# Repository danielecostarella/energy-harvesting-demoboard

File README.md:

WSN Demoboard for Energy Harvesting
===================================

This project aims to develop a demonstration board for integration into a Wireless Sensor Network (WSN) using energy harvesting. The board is optimized in terms of hardware and software to ensure low power consumption, enabling it to be powered through Energy Harvesting. The project is focused on exploring the potential of piezoelectric, solar, and thermoelectric sources for energy harvesting.

less Copy code

Getting Started
---------------

To get started with this project, you will need to have the following hardware and software:

### Hardware

* The demoboard itself
* Piezoelectric, solar, and/or thermoelectric sources (depending on your application)

### Software

* Arduino IDE
* Libraries for the specific sensors used in your project

Installation
------------

1.  Clone this repository to your local machine.
2.  Open the project in Arduino IDE.
3.  Install the required libraries.
4.  Compile and upload the sketch to the demoboard.

Usage
-----

Connect the energy harvesting sources to the demoboard and power it up. The board will automatically begin to harvest energy and power the sensors. Use the specific libraries for your sensors to collect data and transmit it to the WSN.

Contributing
------------

Contributions to this project are welcome! If you find any issues or have suggestions for improvement, please submit a pull request or open an issue.

License
-------

This project is licensed under the [MIT License](https://opensource.org/licenses/MIT). See the `LICENSE` file for details.

Acknowledgments
---------------

* This project was developed as part of a thesis by \[Daniele Costarella\].

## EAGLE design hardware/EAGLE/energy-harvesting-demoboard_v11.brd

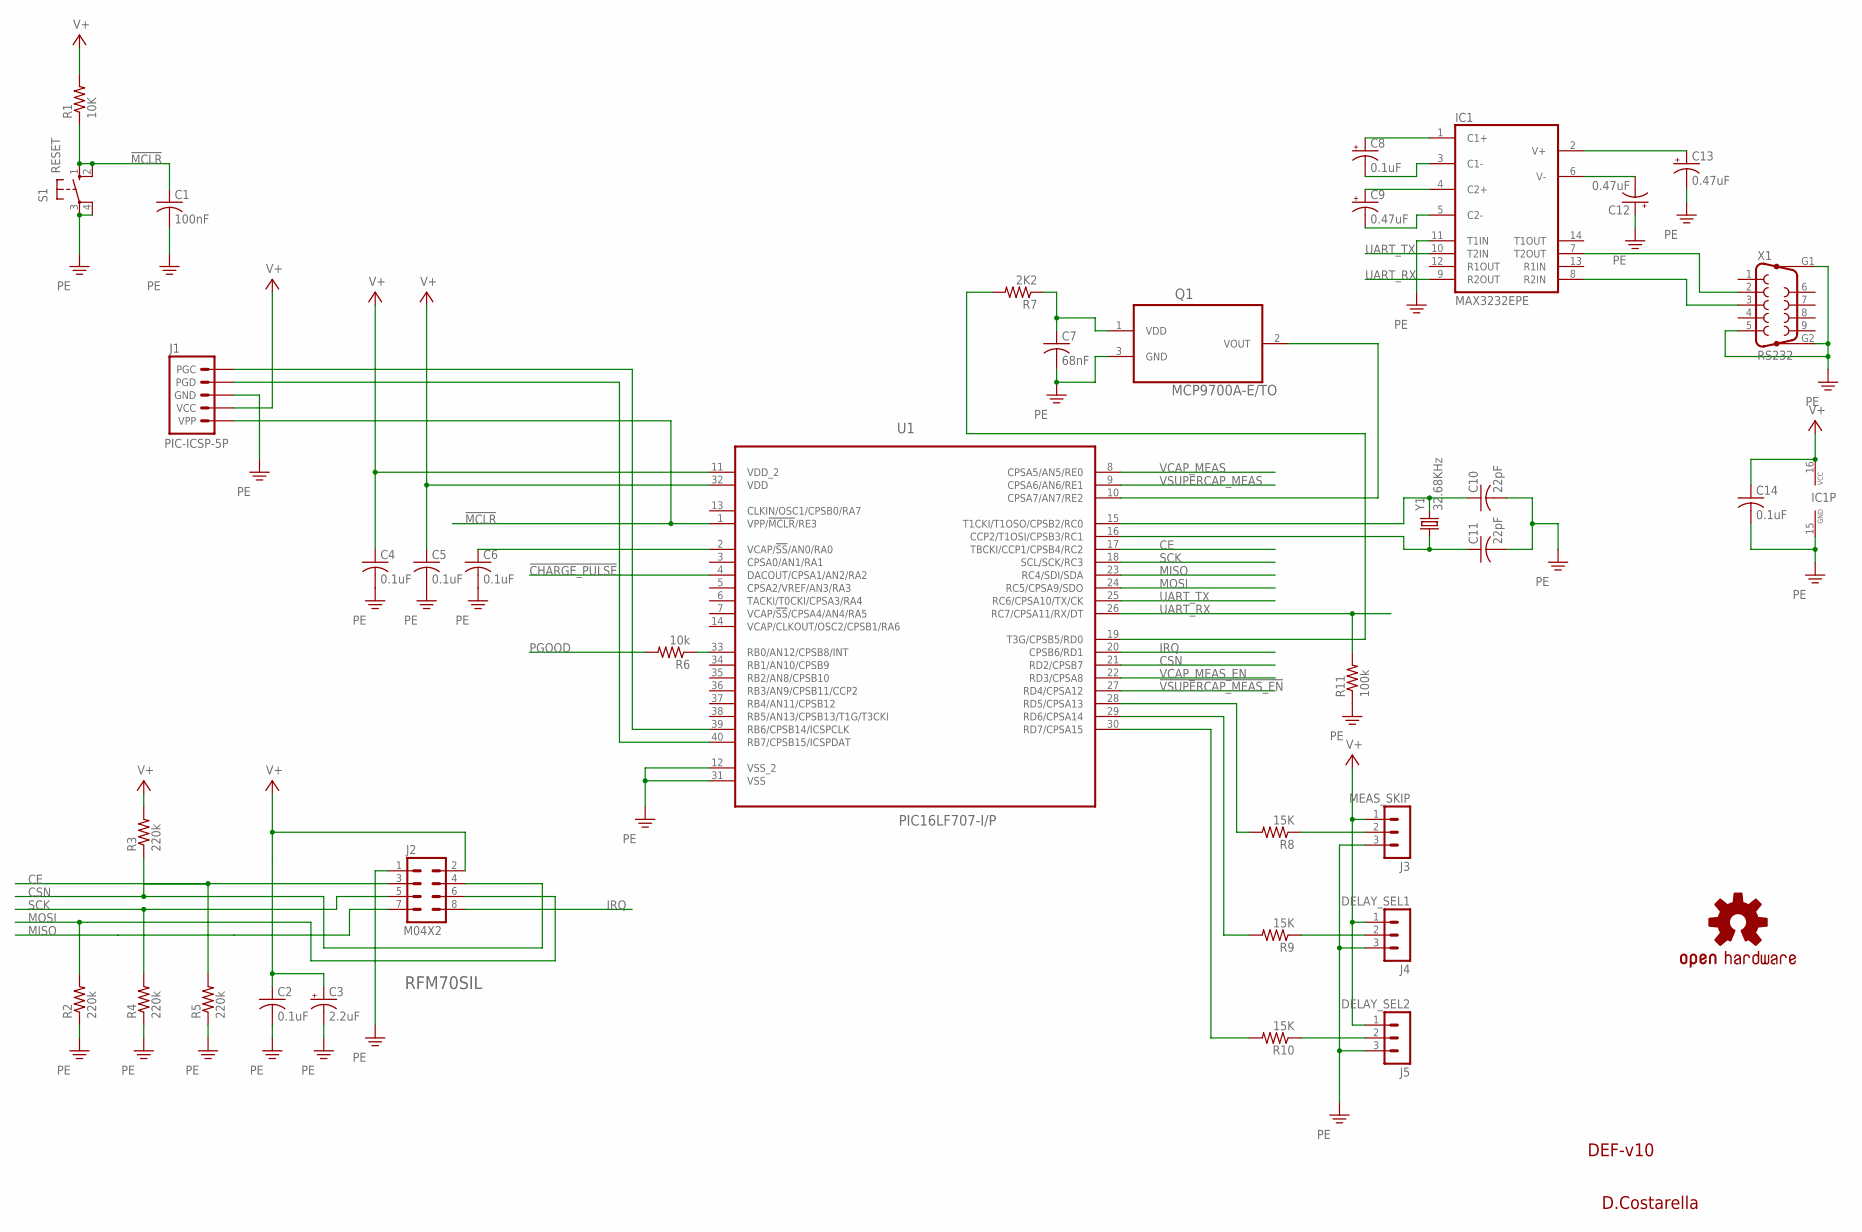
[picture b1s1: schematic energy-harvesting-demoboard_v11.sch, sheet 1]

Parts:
C1: 100nF; C025-025X050
C2, C4, C5, C6: 0.1uF; C050-025X075
C3: 2.2uF; E2,5-5
C7: 68nF; C050-035X075
C8: 0.1uF; E2,5-5
C9, C12, C13: 0.47uF; E2,5-5
C10, C11: 22pF; C025-025X050
C14: 0.1uF; C050-030X075
IC1: MAX3232EPE; DIL16
J1: PIC-ICSP-5P; 1X05
J2: M04X2; 2X4
J3: MEAS_SKIP; MA03-1
J4: DELAY_SEL1; MA03-1
J5: DELAY_SEL2; MA03-1
LOGO1: OSHW-LOGOL; OSHW-LOGO-L
Q1: MCP9700A-E/TO; TO127P254X533-3
R1: 10K; AXIAL-0.4
R2, R3, R4, R5: 220k; AXIAL-0.4
R6: 10k; AXIAL-0.4
R7: 2K2; AXIAL-0.4
R8, R9, R10: 15K; AXIAL-0.4
R11: 100k; AXIAL-0.4
S1: RESET; B3F-10XX
U1: PIC16LF707-I/P; DIP254P1524X635-40
X1: RS232; F09HP
Y1: 32.68KHz; TC26HEZ

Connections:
!CHARGE_PULSE: U1.4 (DACOUT/CPSA1/AN2/RA2); also elsewhere on the board
!MCLR: C1.1, J1.1 (VPP), R1.P$1 (1), S1.1 (S), S1.2 (S1), U1.1 (VPP/!MCLR!/RE3)
!VSUPERCAP_MEAS_EN: U1.27 (RD4/CPSA12); also elsewhere on the board
CE: J2.3, R5.P$2 (2), U1.17 (TBCKI/CCP1/CPSB4/RC2)
CSN: J2.4, R3.P$1 (1), U1.21 (RD2/CPSB7)
IRQ: J2.8, U1.20 (CPSB6/RD1)
MISO: J2.7, U1.23 (RC4/SDI/SDA)
MOSI: J2.6, R2.P$2 (2), U1.24 (RC5/CPSA9/SDO)
unnamed: J1.5 (PGC), U1.39 (RB6/CPSB14/ICSPCLK)
unnamed: J1.4 (PGD), U1.40 (RB7/CPSB15/ICSPDAT)
unnamed: C6.1, U1.2 (VCAP/!SS!/AN0/RA0)
unnamed: C10.1, U1.15 (T1CKI/T1OSO/CPSB2/RC0), Y1.2
unnamed: C11.1, U1.16 (CCP2/T1OSI/CPSB3/RC1), Y1.1
unnamed: Q1.2 (VOUT), U1.10 (CPSA7/AN7/RE2)
unnamed: J3.2, R8.P$1 (1)
unnamed: R8.P$2 (2), U1.28 (RD5/CPSA13)
unnamed: J4.2, R9.P$1 (1)
unnamed: J5.2, R10.P$1 (1)
unnamed: R9.P$2 (2), U1.29 (RD6/CPSA14)
unnamed: R10.P$2 (2), U1.30 (RD7/CPSA15)
unnamed: C7.1, Q1.1 (VDD), R7.P$1 (1)
unnamed: C8.+, IC1.1 (C1+)
unnamed: C8.-, IC1.3 (C1-)
unnamed: C9.+, IC1.4 (C2+)
unnamed: C9.-, IC1.5 (C2-)
unnamed: C12.-, IC1.6 (V-)
unnamed: C13.+, IC1.2 (V+)
unnamed: IC1.8 (R2IN), X1.3
unnamed: IC1.7 (T2OUT), X1.2
unnamed: R6.P$1 (1), U1.33 (RB0/AN12/CPSB8/INT)
PE: C1.2, C2.2, C3.-, C4.2, C5.2, C6.2, C7.2, C10.2, C11.2, C12.+, C13.-, C14.2, IC1.11 (T1IN), IC1.15 (GND), J1.3 (GND), J2.1, J3.3, J4.3, J5.3, Q1.3 (GND), R2.P$1 (1), R4.P$1 (1), R5.P$1 (1), R11.P$1 (1), S1.3, S1.4 (P1), U1.12 (VSS_2), U1.31 (VSS), X1.5, X1.G1, X1.G2; also elsewhere on the board
PGOOD: R6.P$2 (2); also elsewhere on the board
SCK: J2.5, R4.P$2 (2), U1.18 (SCL/SCK/RC3)
SENS_EN: R7.P$2 (2), U1.19 (T3G/CPSB5/RD0)
UART_RX: IC1.9 (R2OUT), R11.P$2 (2), U1.26 (RC7/CPSA11/RX/DT)
UART_TX: IC1.10 (T2IN), U1.25 (RC6/CPSA10/TX/CK)
V+: C2.1, C3.+, C4.1, C5.1, C14.1, IC1.16 (VCC), J1.2 (VCC), J2.2, J3.1, J4.1, J5.1, R1.P$2 (2), R3.P$2 (2), U1.11 (VDD_2), U1.32 (VDD); also elsewhere on the board
VCAP_MEAS: U1.8 (CPSA5/AN5/RE0); also elsewhere on the board
VCAP_MEAS_EN: U1.22 (RD3/CPSA8); also elsewhere on the board
VSUPERCAP_MEAS: U1.9 (CPSA6/AN6/RE1); also elsewhere on the board

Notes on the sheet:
DEF-v10
D.Costarella
RFM70SIL

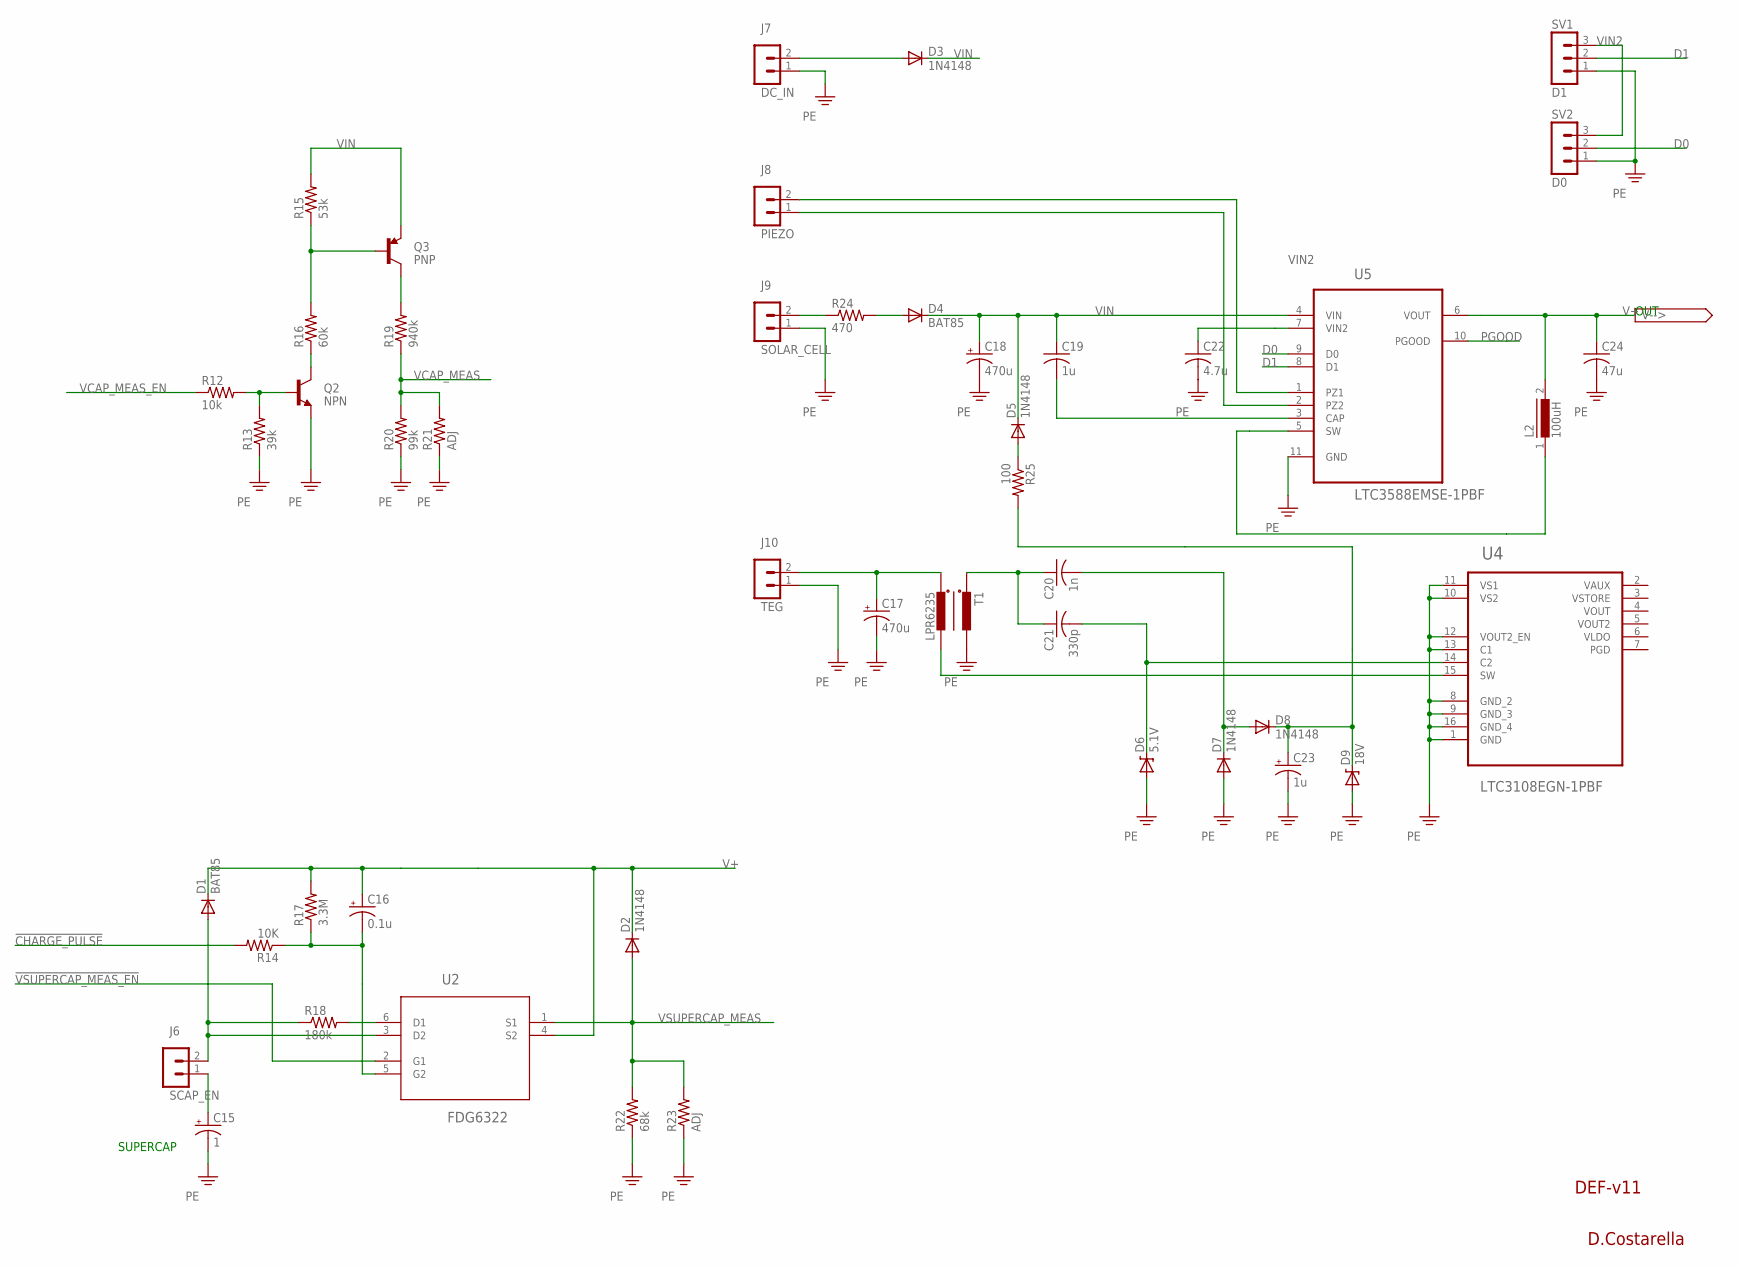
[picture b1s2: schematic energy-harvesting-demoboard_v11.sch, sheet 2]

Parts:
C15: 1; E5-8,5
C16: 0.1u; E2,5-5
C17, C18: 470u; E5-10,5
C19: 1u; C050-035X075
C20: 1n; C050-030X075
C21: 330p; C050-030X075
C22: 4.7u; C025-024X044
C23: 1u; E2,5-6E
C24: 47u; C050-025X075
D1, D4: BAT85; DIODE-1N4148
D2, D7, D8: 1N4148; DIODE-1N4148
D3, D5: 1N4148; SMA-DIODE
D6: 5.1V; DIODE-ZENER
D9: 18V; DIODE-ZENER
J6: SCAP_EN; MA02-1
J7: DC_IN; MA02-1
J8: PIEZO; MA02-1
J9: SOLAR_CELL; MA02-1
J10: TEG; MA02-1
L2: 100uH; DR125
Q2: NPN; TO-92
Q3: PNP; TO-92
R12: 10k; AXIAL-0.4
R13: 39k; AXIAL-0.4
R14: 10K; AXIAL-0.4
R15: 53k; AXIAL-0.4
R16: 60k; AXIAL-0.4
R17: 3.3M; AXIAL-0.4
R18: 180k; AXIAL-0.4
R19: 940k; AXIAL-0.4
R20: 99k; AXIAL-0.4
R21, R23: ADJ; AXIAL-0.4
R22: 68k; AXIAL-0.4
R24: 470; AXIAL-0.4
R25: 100; AXIAL-0.4
SV1: D1; MA03-1
SV2: D0; MA03-1
T1: LPR6235
U2: FDG6322; SOT65P210X110-6N
U4: LTC3108EGN-1PBF; SOP63P600X175-16N
U5: LTC3588EMSE-1PBF; SOP50P490X110-11N

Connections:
!CHARGE_PULSE: R14.P$2 (2); also elsewhere on the board
!VSUPERCAP_MEAS_EN: U2.2 (G1); also elsewhere on the board
D0: SV2.2, U5.9 (D0)
D1: SV1.2, U5.8 (D1)
unnamed: Q2.2 (B), R12.P$2 (2), R13.P$2 (2)
unnamed: Q2.1 (C), R16.P$1 (1)
unnamed: Q3.2 (B), R15.P$1 (1), R16.P$2 (2)
unnamed: J8.1, U5.2 (PZ2)
unnamed: Q3.3 (C), R19.P$2 (2)
unnamed: D1.A, J6.2, R18.P$1 (1), U2.3 (D2)
unnamed: R18.P$2 (2), U2.6 (D1)
unnamed: J9.2, R24.P$1 (1)
unnamed: J8.2, U5.1 (PZ1)
unnamed: L2.1, U5.5 (SW)
unnamed: C19.2, U5.3 (CAP)
unnamed: C15.+, J6.1
unnamed: C23.+, D8.C, D9.P$1 (C), R25.P$2 (2)
unnamed: C21.2, D6.P$1 (C), U4.14 (C2)
unnamed: D3.A, J7.2
unnamed: C17.+, J10.2, T1.P$1 (1)
unnamed: D5.A, R25.P$1 (1)
unnamed: C20.2, D7.C, D8.A
unnamed: C16.-, R14.P$1 (1), R17.P$1 (1), U2.5 (G2)
unnamed: D4.A, R24.P$2 (2)
unnamed: T1.P$2 (2), U4.15 (SW)
unnamed: C20.1, C21.1, T1.P$4 (4)
PE: C15.-, C17.-, C18.-, C22.2, C23.-, C24.2, D6.P$2 (A), D7.A, D9.P$2 (A), J7.1, J9.1, J10.1, Q2.3 (E), R13.P$1 (1), R20.P$1 (1), R21.P$1 (1), R22.P$1 (1), R23.P$1 (1), SV1.1, SV2.1, T1.P$3 (3), U4.1 (GND), U4.8 (GND_2), U4.9 (GND_3), U4.10 (VS2), U4.11 (VS1), U4.12 (VOUT2_EN), U4.13 (C1), U4.16 (GND_4), U5.11 (GND); also elsewhere on the board
PGOOD: U5.10 (PGOOD); also elsewhere on the board
V+: C16.+, C24.1, D1.C, D2.C, L2.2, R17.P$2 (2), U2.4 (S2), U5.6 (VOUT); also elsewhere on the board
VCAP_MEAS: R19.P$1 (1), R20.P$2 (2), R21.P$2 (2); also elsewhere on the board
VCAP_MEAS_EN: R12.P$1 (1); also elsewhere on the board
VIN: C18.+, C19.1, D3.C, D4.C, D5.C, Q3.1 (E), R15.P$2 (2), U5.4 (VIN)
VIN2: C22.1, SV1.3, SV2.3, U5.7 (VIN2)
VSUPERCAP_MEAS: D2.A, R22.P$2 (2), R23.P$2 (2), U2.1 (S1); also elsewhere on the board

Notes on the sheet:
OUT
SUPERCAP
DEF-v11
D.Costarella

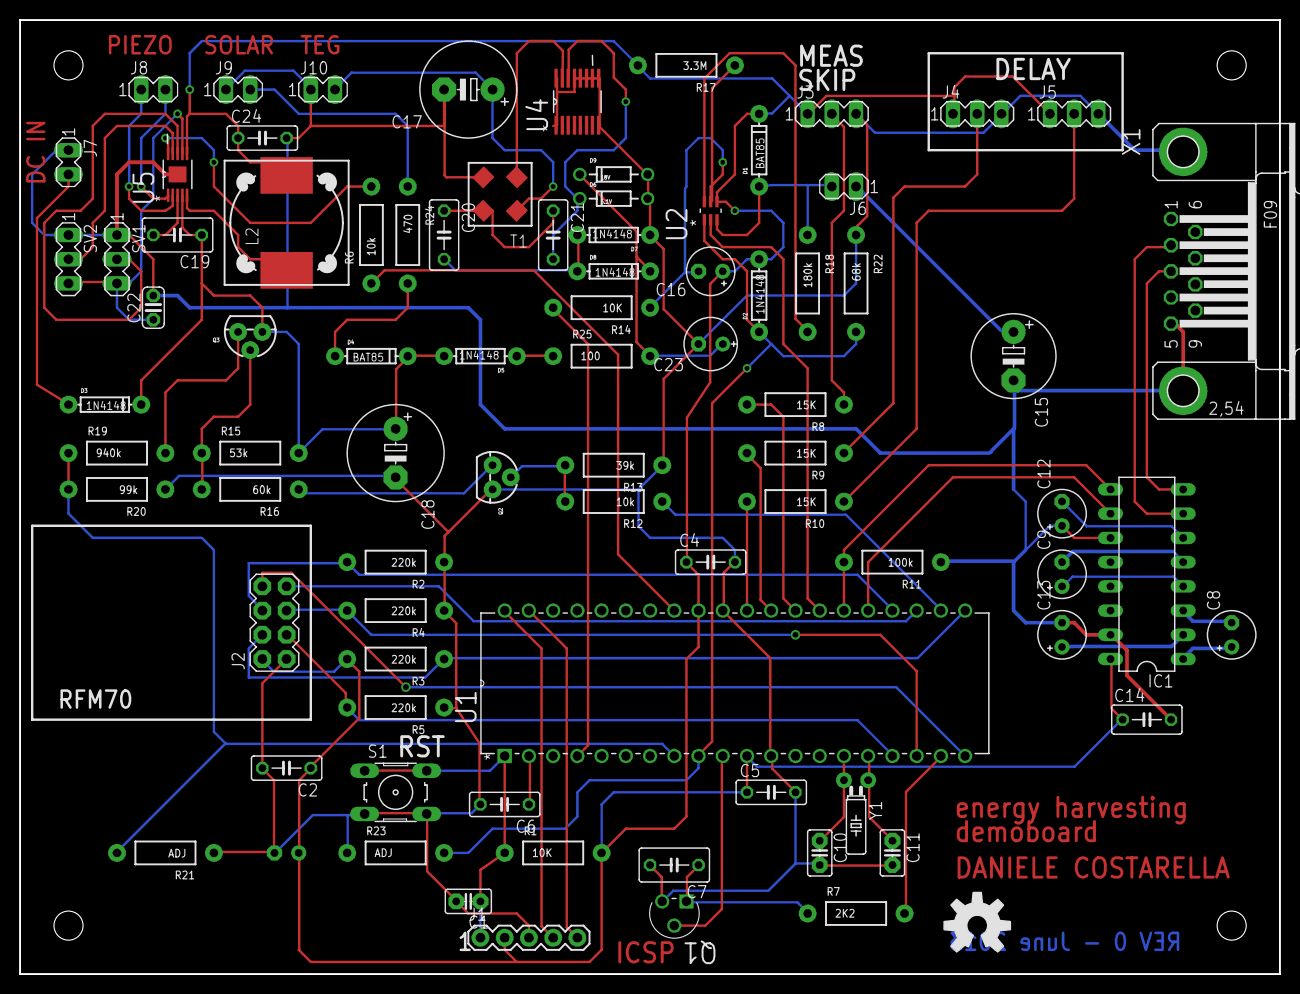
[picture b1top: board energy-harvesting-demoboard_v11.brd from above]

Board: 2 copper layers, 132.1 x 100.0 mm, 84 parts (1 on the bottom side), 66 nets.

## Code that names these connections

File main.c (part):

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#pragma config WDTE = OFF   // Watchdog Timer Enable bit (WDT disabled and can
                            // be enabled by SWDTEN bit of the WDTCON register)
#pragma config PWRTE = OFF  // Power-up Timer Enable bit (PWRT disabled)
#pragma config MCLRE = ON   // RE3/MCLR pin function select bit (RE3/MCLR pin
                            // function is MCLR)
#pragma config CP = OFF     // Code Protection bit (Program memory code
                            // protection is disabled)
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int16_t timelapse_count = 0;
unsigned int charge_time;           // int16_t
unsigned int charge_pulse;          // pulse length in ms
float charge_pulse_float = 10;      // charge_pulse = (int)charge_pulse_float

unsigned int dac_value = 26; //era 25

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    FVRCONbits.ADFVR=1;
    while(!FVRCONbits.FVRRDY);  // wait for a stable FVR
    ADCON0bits.ADON=1;
    PORTDbits.RD0=1;            // mcp9700a power up
    WAIT_MS(1);
    ADCON0bits.GO_nDONE=1;
    while(ADCON0bits.GO_nDONE);
    value = ADRES;
    ADCON0bits.ADON=0;
    PORTDbits.RD0=0;            // turn off mcp9700a
    FVRCONbits.FVREN=0;         // 0 = Fixed Voltage Reference is disabled
    return value;
}
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    ADCON0bits.CHS=5;
    FVRCONbits.ADFVR=2;
    ADCON0bits.ADON=1;
    PORTDbits.RD3=1;            // Select Vstorage measurement
    WAIT_MS(1);
    ADCON0bits.GO_nDONE=1;
    while(ADCON0bits.GO_nDONE);
    value = ADRES;
    ADCON0bits.ADON=0;
    PORTDbits.RD3=0;            // Turn off switch for Vstorage measure
    FVRCONbits.FVREN=0;         // 0 = Fixed Voltage Reference is disabled
    return value;
}
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    FVRCONbits.ADFVR=1;
    while(!FVRCONbits.FVRRDY);  // wait for a stable FVR
    ADCON0bits.ADON=1;
    PORTDbits.RD4=1;            // Select V supercap measurement pin
    WAIT_MS(1);
    ADCON0bits.GO_nDONE=1;
    while(ADCON0bits.GO_nDONE);
    value = ADRES;
    ADCON0bits.ADON=0;
    PORTDbits.RD4=0;            // Turn off switch for V supercap measure
    FVRCONbits.FVREN=0;         // 0 = Fixed Voltage Reference is disabled
    return value;
}
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/*****************************************************************************
 * Function:        uartInit()
 *
 * Description:     Initializes UART module. Set RC7 pin as UART RX input pin
 *                  and RC6 as UART TX output pin. Enables high speed and sets
 *                  boardrate
 *
 ****************************************************************************/
void uartInit(void) {
    TRISCbits.TRISC7=1;     // RC7 = UART RX pin input
    TRISCbits.TRISC6=0;     // RC6 = UART TX pin output
    TXSTA=0x02;             // High speed
    RCSTA=0x00;
    //BAUDCON=0x00;
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    /* supercap meas */
    TRISDbits.TRISD4=0;
    ANSELDbits.ANSD4=0;
    PORTDbits.RD4=0;        

    // dac init
    TRISAbits.TRISA2=0;     // RA2 = DAC voltage output
    ANSELAbits.ANSA2=0;
    SCAP_MOS=1;


    /* RFM70 pins */
    ANSELCbits.ANSC2=0;     // CE as digital
    ANSELDbits.ANSD2=0;     // CSN as digital
    ANSELCbits.ANSC5=0;     // MOSI as digital
    ANSELDbits.ANSD1=0;     // IRQ as digital
    TRISCbits.TRISC2=0;     // CE
    TRISDbits.TRISD2=0;     // CSN
    TRISCbits.TRISC3=0;     // SCK
    TRISCbits.TRISC5=0;     // MOSI
    TRISCbits.TRISC4=1;     // MISO
    TRISDbits.TRISD1=1;     // IRQ
    CE=0;
    CSN=1;
    SCK=0;
    MOSI=0;

    /* MCP9700A */
    TRISDbits.TRISD0=0;     // MCP9700A power
    ANSELDbits.ANSD0=0;     // pin RD0 as digital
    TRISEbits.TRISE2=1;     // MCP9700A Vout
    ANSELEbits.ANSE2=1;     // set RE2 pin as analog
    TRISEbits.TRISE0=1;     // RE0 as input
    ANSELEbits.ANSE0=0;     // set RE0 pin as analog (Vstorage)
    PORTDbits.RD0=0;        // turn off MCP9700A

    /* Vstorage monitor */
    TRISEbits.TRISE0=1;     // for Vstorage measuring
    ANSELEbits.ANSE0=1;     // pin RE0 as analog
    TRISDbits.TRISD3=0;     // enable Vstorage measure
    PORTDbits.RD3=0;        // set to low

    /* Skip measure */
    TRISDbits.TRISD5=1;     // RD5 as input
    ANSELDbits.ANSD5=0;     // RD5 as digital
    
    /* and number of SLEEP (Set delay) */
    TRISDbits.TRISD6=1;
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    /* Vsupercap measure */
    TRISEbits.TRISE1=1;
    ANSELEbits.ANSE1=1;
    PORTEbits.RE1=0;

    /***************************** NOT USED PINS *****************************/
    TRISAbits.TRISA0=0;     //per PIC16LF707
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    ANSELAbits.ANSA5=0;
    ANSELAbits.ANSA6=0;
    ANSELAbits.ANSA7=0;
    PORTAbits.RA0=0;        //per PIC16LF707
    PORTAbits.RA1=0;
    PORTAbits.RA3=0;
    PORTAbits.RA4=0;
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
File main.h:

/*****************************************************************************
 * File:        main.h
 * Author:      Daniele Costarella <daniele.costarella@gmail.com>
 *
 * Processor:   PIC16
 *              tested with 16LF707, 16F707
 * Compiler:    Microchip XC8 v1.12 or higher
 *
 * Released on: June, 2013
 *
 *****************************************************************************
 * File description:
 *
 * Energy Harvesting Demoboard firmware
 * Header file for main.c
 *
 * For new versions of this code please visit:
 * https://github.com/blackbliss/energy-harvesting-demoboard
 *
 * Detailed information can also be found on my master thesis [IT]
 *
 *****************************************************************************/

#ifndef MAIN_H
#define	MAIN_H

#define _XTAL_FREQ 8000000L
#define WAIT_US( x ) _delay( x * ( _XTAL_FREQ / 4000000))
#define WAIT_MS( x ) _delay( x * ( _XTAL_FREQ / 4000))

/*********************************** RFM70 ***********************************/
#define CE      PORTCbits.RC2
#define CSN     PORTDbits.RD2
#define SCK     PORTCbits.RC3
#define MISO    PORTCbits.RC4
#define MOSI    PORTCbits.RC5
#define IRQ     PORTDbits.RD1

#define SKIP_MEASURE    PORTDbits.RD5
#define PGOOD           PORTBbits.RB0
#define SCAP_MOS        PORTAbits.RA2   // 0: enabled; 1: disabled

#endif	/* MAIN_H */

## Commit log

2013-02-15 Starting project... first commit
2013-02-15 Added 'DEFINE' for SPI commands in rfm70.h
2013-02-18 Start writing bit-bang functions
2013-03-03 ISR and ADC working. New processor PIC16F707
2013-03-04 Riduzione ritardi e test oscilloscopio
2013-03-08 Added MCP9700A + code
2013-03-08 Added Vcap check, send temperature and vcap to be converted on the receiver side (40-50 uA in sleep mode)
2013-03-08 Added Vstorage check before rfm70 init
2013-03-08 Risolto bug alla funzione powerdown() che faceva consumare alternativamente 100uA/40uA al power-up
2013-03-10 Added SLEEPCOUNT. The node send values together with the number (16 bit) of that acquisition
2013-03-12 Regolazione ritarti, rivisto il contatore per il numero del pacchetto inviato
2013-03-12 Aggiunto controllo ritardi, pin per il salto del controllo sulla tensione Vstorage, eliminato LED e spostato pin di alimentazione dell'mcp9700a da RE1 a RD0 (ex LED_PIN). Aggiunto invio dello status 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
2013-03-14 Pin non utilizzati impostati come uscite nulle, ridotto il ritardo della funzione SPI_RW
2013-03-17 Aggiunta funzionel sleep() con possibilità di impulso di carica in attesa di futura modulazione
2013-03-20 Inserita direttiva #DEFINE per tensioni di soglia + modifica calcolo energia
2013-04-24 DAC config added
2013-05-02 Passaggio a PIC16LF707.
2013-05-11 Somma dell'energia per invii successivi, invio dello stato dei DIP Switch corretto, carica attraverso il MOSFET e DAC, consumo 20uA
2013-05-12 Aggiunta algoritmo di carica per SUPERCAP
2013-05-13 Rimosso codice per far rimanere il MOS sempre ON
2013-05-13 Risolto bug al controllo dell'impulso di carica
2013-05-14 Nuovo algoritmo basato su percentuale per lunghezza dell'impulso di carica
2013-05-20 Aggiunto bit di status per la presenza dell'alimentazione. Ora il nodo è in grado di avviarsi grazie al solo supercondensatore se opportunamente carico.
2013-05-21 Misura del supercap con MOS ON; FVR Ready bit per le misure fatte dall'ADC; miglioramento dell'algoritmo per la riattivazione con power supply
2013-05-26 PGOOD su RB0; gestione dell'invio quando scampare la tensione (c'era un bug che portava a un picco sul primo invio in backup); temp => energy; risolto il problema dell'accumulo dei valori di energia 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
2013-05-26 Il byte jumper-stat contiene ora anche PGOOD (bit 6)
2013-05-26 Riferimento di tensione (FVR) attivo 'solo' durante le misure => ottenuto ulteriore riduzione di corrente assorbita
2013-05-27 Azzeramento del valore della variabile energy dopo ogni invio del pacchetto
2013-05-28 Pulizia del codice, rimozione di alcuni commenti, aggiunti define, funzione boardInit per la configurazione dei pin
2013-05-29 Nuova Define TX_PACKET_LEN, rimossa funzione adcRead inutilizzata, pulizia codice
2013-06-08 Pulizia codice
2013-06-09 Ora invia anche il pacchetto 0; invio anche quando la tensione Vin sta salendo
2013-06-26 Release version
2018-03-21 Updated project description in README file
2018-03-21 Update project description in README file
2018-03-21 Remove built files
2018-03-21 Add gitignore file
2018-03-21 Update gitignore file
2018-03-21 Remove stat file
2018-03-21 Update link in the header
2018-03-21 Update project files and properties
2018-03-21 [minor] Update comments
2018-03-24 Move code to firmware directory
2018-03-24 Add board gerber files
2018-03-24 Add schematics and board Eagle files
2018-03-24 Add schematics and board file exported to PDF
2023-03-04 Adjust README file since the linked website is no longer available

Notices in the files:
main.c:
This program is free software: you can redistribute it and/or modify
it under the terms of the GNU General Public License as published by
the Free Software Foundation, either version 3 of the License, or
(at your option) any later version.
parts and their libraries:
SparkFun-FreqCtrl: Licensing: CC v3.0 Share-Alike You are welcome to use this library for commercial purposes.
